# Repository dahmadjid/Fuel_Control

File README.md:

# Fuel_Control
Schlumberger Fuel Control

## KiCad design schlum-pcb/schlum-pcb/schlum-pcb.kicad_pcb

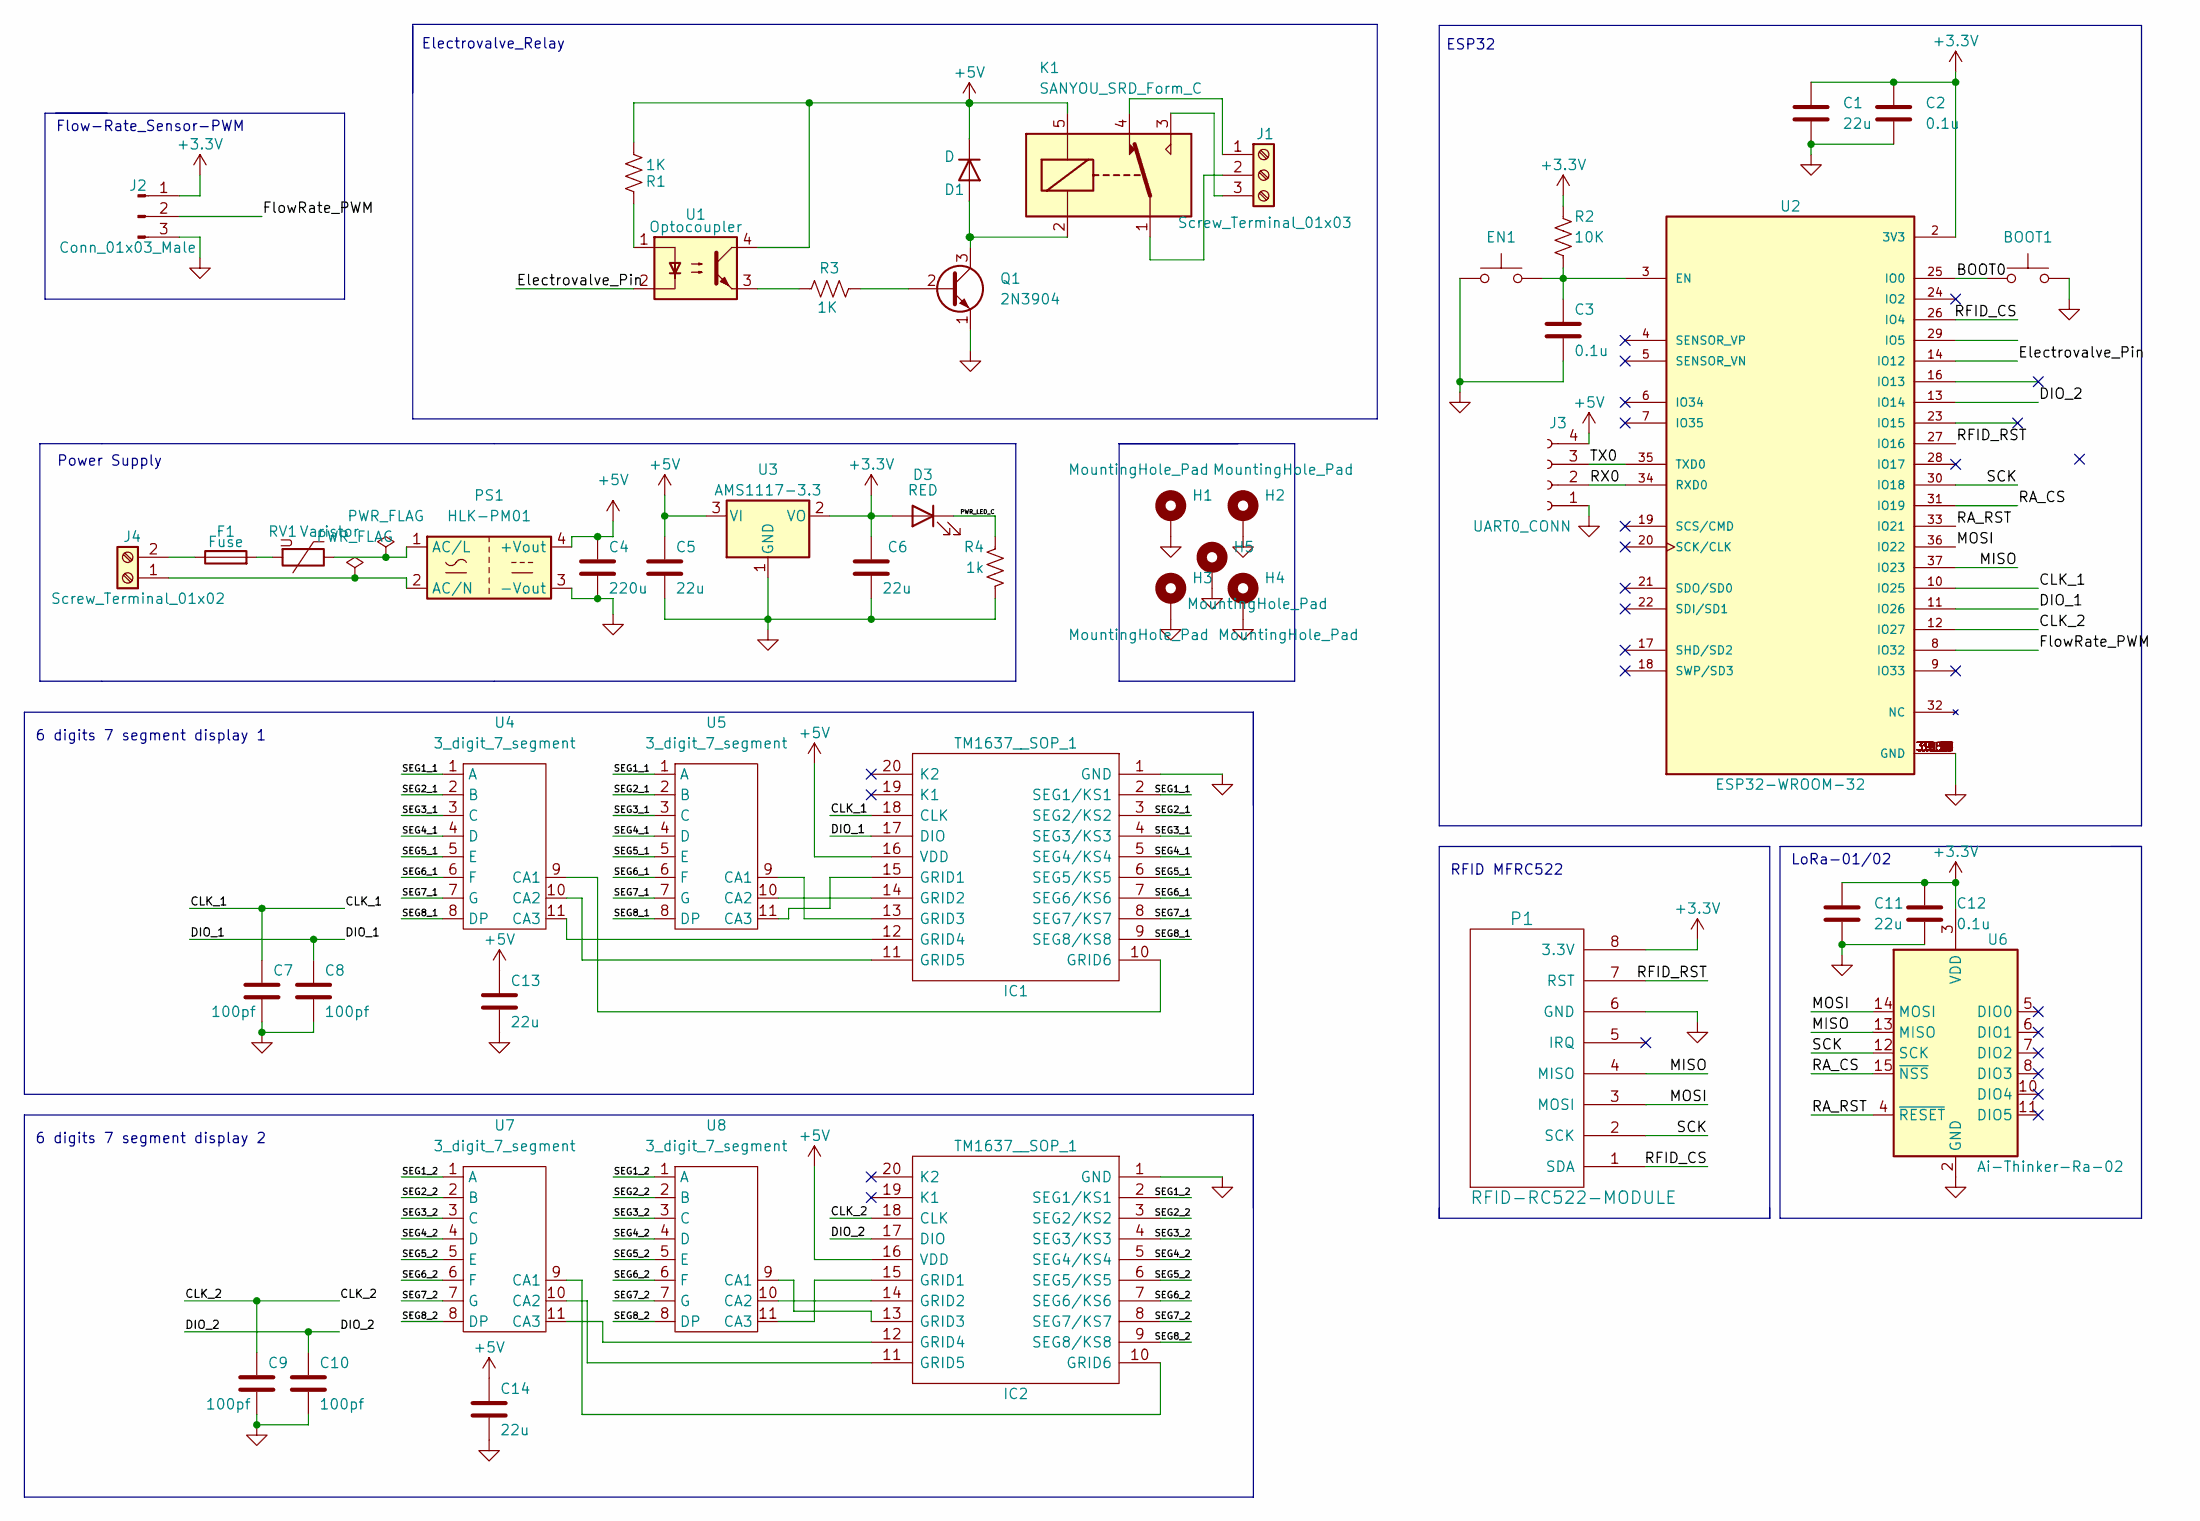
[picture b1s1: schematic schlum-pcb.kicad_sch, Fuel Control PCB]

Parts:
BOOT1: SW_Push; SW_SPST_CK_RS282G05A3
C1, C5, C6, C11, C13, C14: 22u; C_0603_1608Metric
C2, C3, C12: 0.1u; C_0603_1608Metric
C4: 220u; C_Radial_D8.0mm_H11.5mm_P3.50mm
C7, C8, C9, C10: 100pf; C_0402_1005Metric
D1: D; D_0603_1608Metric
D3: RED; LED_D5.0mm
EN1: SW_Push; SW_SPST_CK_RS282G05A3
F1: Fuse; Fuseholder_Cylinder-5x20mm_Schurter_0031_8201_Horizontal_Op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
H1, H2, H3, H4, H5: MountingHole_Pad; MountingHole_4.3mm_M4_ISO14580_Pad
IC1, IC2: TM1637__SOP_1; SOIC127P1045X280-20N; Manufacturer_Part_Number TM1637 (SOP)
J1: Screw_Terminal_01x03; TerminalBlock_bornier-3_P5.08mm
J2: Conn_01x03_Male; PinHeader_1x03_P2.54mm_Vertical
J3: UART0_CONN; PinHeader_1x04_P2.54mm_Vertical
J4: Screw_Terminal_01x02; TerminalBlock_bornier-2_P5.08mm
K1: SANYOU_SRD_Form_C; Relay_SPDT_SANYOU_SRD_Series_Form_C
P1: RFID-RC522-MODULE; PinSocket_1x08_P2.54mm_Vertical
PS1: HLK-PM01; Converter_ACDC_HiLink_HLK-PMxx
Q1: 2N3904; TO-92_Inline
R1, R3: 1K; R_0402_1005Metric
R2: 10K; R_0402_1005Metric
R4: 1k; R_0402_1005Metric
RV1: Varistor; RV_Disc_D12mm_W5.1mm_P7.5mm
U1: Optocoupler; DIP-4_W7.62mm
U2: ESP32-WROOM-32; MODULE_ESP32-WROOM-32; PARTREV 2.9
U3: AMS1117-3.3; SOT-223-3_TabPin2
U4, U5, U7, U8: 3_digit_7_segment; 3 digit 7 segment
U6: Ai-Thinker-Ra-02; Ai-Thinker-Ra-01-LoRa

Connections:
+3.3V: C1.1, C2.1, C6.1, C11.1, C12.1, D3.2 (A), J2.1, P1.8 (3.3V), R2.1, U2.2 (3V3), U3.2 (VO), U6.3 (VDD)
+5V: C4.1, C5.1, C13.1, C14.1, D1.1 (K), IC1.16 (VDD), IC2.16 (VDD), J3.4, K1.5, PS1.4 (+Vout), R1.2, U1.4, U3.3 (VI)
/BOOT0: BOOT1.2, U2.25 (IO0)
/CLK_1: C7.1, IC1.18 (CLK), U2.10 (IO25)
/CLK_2: C9.1, IC2.18 (CLK), U2.12 (IO27)
/DIO_1: C8.1, IC1.17 (DIO), U2.11 (IO26)
/DIO_2: C10.1, IC2.17 (DIO), U2.13 (IO14)
/Electrovalve_Pin: U1.2, U2.14 (IO12)
/FlowRate_PWM: J2.2, U2.8 (IO32)
/MISO: P1.4 (MISO), U2.37 (IO23), U6.13 (MISO)
/MOSI: P1.3 (MOSI), U2.36 (IO22), U6.14 (MOSI)
/PWR_LED_C: D3.1 (K), R4.1
/RA_CS: U2.31 (IO19), U6.15 (~NSS)
/RA_RST: U2.33 (IO21), U6.4 (~RESET)
/RFID_CS: P1.1 (SDA), U2.26 (IO4)
/RFID_RST: P1.7 (RST), U2.27 (IO16)
/RX0: J3.2, U2.34 (RXD0)
/SCK: P1.2 (SCK), U2.30 (IO18), U6.12 (SCK)
/SEG1_1: IC1.2 (SEG1/KS1), U4.1 (A), U5.1 (A)
/SEG1_2: IC2.2 (SEG1/KS1), U7.1 (A), U8.1 (A)
/SEG2_1: IC1.3 (SEG2/KS2), U4.2 (B), U5.2 (B)
/SEG2_2: IC2.3 (SEG2/KS2), U7.2 (B), U8.2 (B)
/SEG3_1: IC1.4 (SEG3/KS3), U4.3 (C), U5.3 (C)
/SEG3_2: IC2.4 (SEG3/KS3), U7.3 (C), U8.3 (C)
/SEG4_1: IC1.5 (SEG4/KS4), U4.4 (D), U5.4 (D)
/SEG4_2: IC2.5 (SEG4/KS4), U7.4 (D), U8.4 (D)
/SEG5_1: IC1.6 (SEG5/KS5), U4.5 (E), U5.5 (E)
/SEG5_2: IC2.6 (SEG5/KS5), U7.5 (E), U8.5 (E)
/SEG6_1: IC1.7 (SEG6/KS6), U4.6 (F), U5.6 (F)
/SEG6_2: IC2.7 (SEG6/KS6), U7.6 (F), U8.6 (F)
/SEG7_1: IC1.8 (SEG7/KS7), U4.7 (G), U5.7 (G)
/SEG7_2: IC2.8 (SEG7/KS7), U7.7 (G), U8.7 (G)
/SEG8_1: IC1.9 (SEG8/KS8), U4.8 (DP), U5.8 (DP)
/SEG8_2: IC2.9 (SEG8/KS8), U7.8 (DP), U8.8 (DP)
/TX0: J3.3, U2.35 (TXD0)
GND: BOOT1.1, C1.2, C2.2, C3.2, C4.2, C5.2, C6.2, C7.2, C8.2, C9.2, C10.2, C11.2, C12.2, C13.2, C14.2, EN1.1, H1.1, H2.1, H3.1, H4.1, H5.1, IC1.1 (GND), IC2.1 (GND), J2.3, J3.1, P1.6 (GND), PS1.3 (-Vout), Q1.1 (E), R4.2, U2.1 (GND), U2.15 (GND), U2.38 (GND), U2.39_1 (GND), U2.39_2 (GND), U2.39_3 (GND), U2.39_4 (GND), U2.39_5 (GND), U2.39_6 (GND), U2.39_7 (GND), U2.39_8 (GND), U2.39_9 (GND), U2.39_10 (GND), U2.39_11 (GND), U2.39_12 (GND), U2.39_13 (GND), U2.39_14 (GND), U2.39_15 (GND), U2.39_16 (GND), U2.39_17 (GND), U2.39_18 (GND), U2.39_19 (GND), U2.39_20 (GND), U2.39_21 (GND), U3.1 (GND), U6.1 (GND), U6.2 (GND), U6.9 (GND), U6.16 (GND)
unnamed: C3.1, EN1.2, R2.2, U2.3 (EN)
unnamed: D1.2 (A), K1.2, Q1.3 (C)
unnamed: F1.1, J4.2
unnamed: F1.2, RV1.2
unnamed: IC1.11 (GRID5), U4.10 (CA2)
unnamed: IC1.13 (GRID3), U5.9 (CA1)
unnamed: IC1.14 (GRID2), U5.10 (CA2)
unnamed: IC1.15 (GRID1), U5.11 (CA3)
unnamed: IC2.11 (GRID5), U7.10 (CA2)
unnamed: IC2.13 (GRID3), U8.9 (CA1)
unnamed: IC2.14 (GRID2), U8.10 (CA2)
unnamed: IC2.15 (GRID1), U8.11 (CA3)
unnamed: J1.1, K1.4
unnamed: J1.2, K1.1
unnamed: J1.3, K1.3
unnamed: J4.1, PS1.2 (AC/N)
unnamed: PS1.1 (AC/L), RV1.1
unnamed: Q1.2 (B), R3.2
unnamed: R1.1, U1.1
unnamed: R3.1, U1.3
unnamed: IC1.10 (GRID6), U4.9 (CA1)
unnamed: IC1.12 (GRID4), U4.11 (CA3)
unnamed: IC2.10 (GRID6), U7.9 (CA1)
unnamed: IC2.12 (GRID4), U7.11 (CA3)

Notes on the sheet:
Electrovalve_Relay
6 digits 7 segment display 2
LoRa-01/02
6 digits 7 segment display 1
RFID MFRC522
ESP32
Power Supply
Flow-Rate_Sensor-PWM

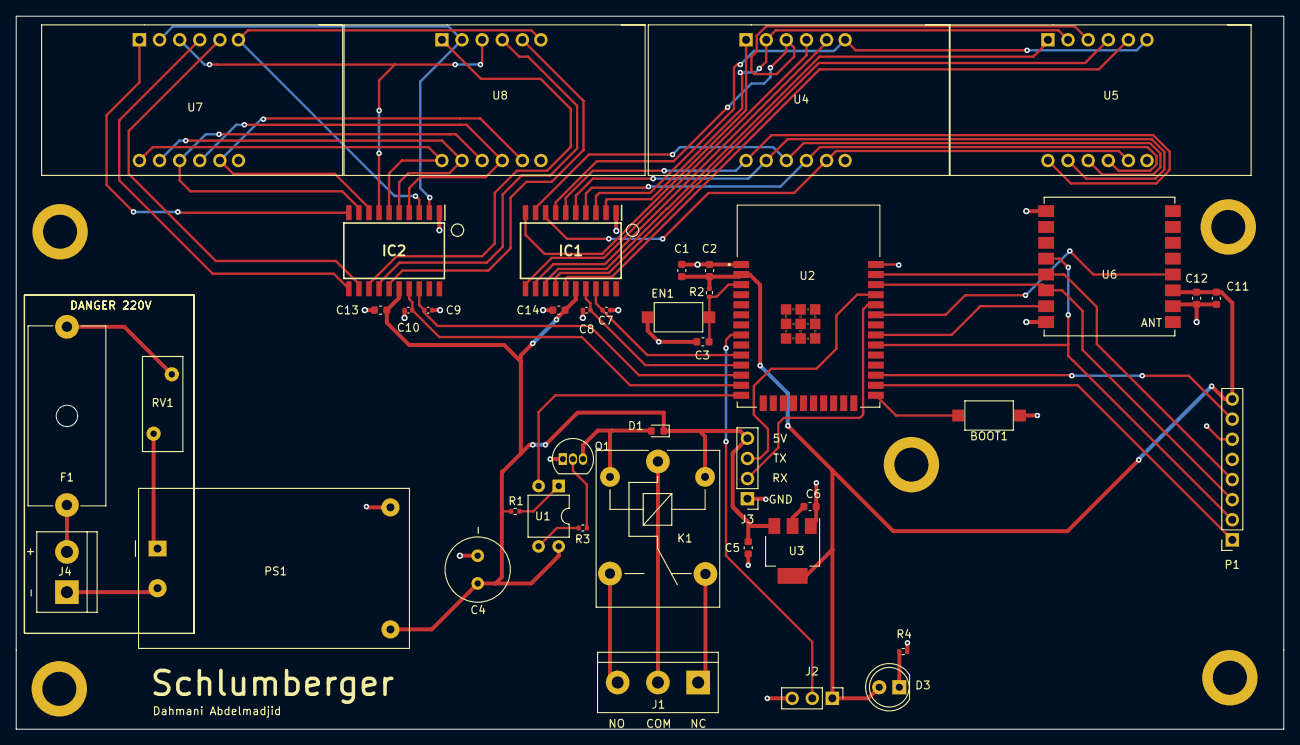
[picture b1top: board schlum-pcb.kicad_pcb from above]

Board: 2 copper layers, 160.0 x 90.0 mm, 47 parts (0 on the bottom side), 60 nets.

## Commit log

2022-01-03 components and py
2022-07-09 schematic only
2022-07-21 idk how i forgot to upload this
